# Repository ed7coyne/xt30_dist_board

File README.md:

This is a simple design for a xt30 based power distribution block. 

It is sized to fit under the seat of a Husqvarna 701 enduro but is also handy in some other situations, like mini-lab. 

This uses XT30PW right angle surface mount connectors which are widely available and very strong. 

This assumes "male" will be hot as the contacts are protected and "female" will be cold as the contacts could allow shorting. As such there is a female input at the short side of the board and then all male outputs along the other edges.

If you just want one the .zip file here can be uploaded to a fab like jlcpcb and it contains the gerbers and drill files needed to have one made. the price is pretty reasonable.

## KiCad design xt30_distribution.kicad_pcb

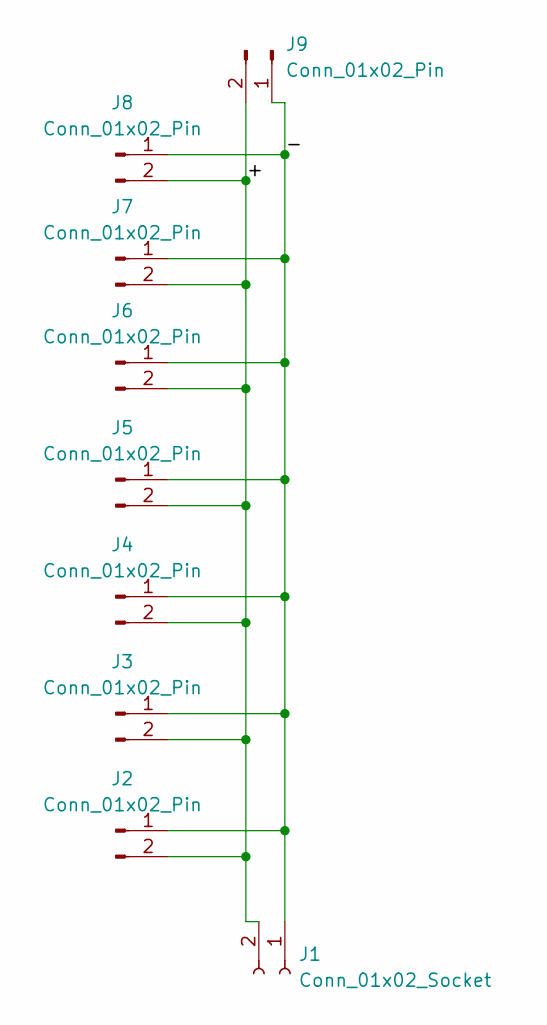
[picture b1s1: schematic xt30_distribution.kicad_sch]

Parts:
J1: Conn_01x02_Socket; AMASS_XT30PW-M_1x02_P2.50mm_Horizontal
J2, J3, J4, J5, J6, J7, J8, J9: Conn_01x02_Pin; AMASS_XT30PW-F_1x02_P2.50mm_Horizontal

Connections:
/+: J1.2, J2.2, J3.2, J4.2, J5.2, J6.2, J7.2, J8.2, J9.2
/-: J1.1, J2.1, J3.1, J4.1, J5.1, J6.1, J7.1, J8.1, J9.1

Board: 2 copper layers, 9 parts (0 on the bottom side), 2 nets, no tracks yet.

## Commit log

2025-03-30 Initial import
